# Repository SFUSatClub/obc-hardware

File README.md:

# OBC Hardware #

**demoboard_v1:** test board featuring RTC, flash memory, watchdog and SEL protection, to be tested with the TMS570LS0432 Launchpad board.

**OBC_prototypeA:** design for PC104 compliant OBC prototype, including onboard MCU, flash memory, SEL protection and power supplies. Includes all features of demoboard, interfaced to TMS570LS0714 MCU.

**Kicad-Lib:** SFUSat's common footprint and schematic symbol library.

## Getting started: ##
Clone this repo In the obc-hardware directory, run git submodule init In the obc-hardware directory, run git submodule update

Open KiCAD, navigate to the project you're interested in.
In EESchema, go to Preferences > Component Libraries
1. "Add" a user defined search path, select the KiCad-Lib directory in the obc-hardware directory
2. "Add" component library files and select the SFUSat.lib file in the KiCad-Lib folder
3. Press ok.

**Note:** issues may arise when using relative paths. Select absolute paths by choosing "No" when asked if you want to use a relative path

Exit back to the KiCad home window and go to Pcbnew > Preferences > Footprint Libraries Manager > "Project Specific Libraies" tab:

1. "Add Library"
2. Nickname: SFUSat
3. Library Path: ${KIPRJMOD}/KiCad-Lib/SFUSat.pretty

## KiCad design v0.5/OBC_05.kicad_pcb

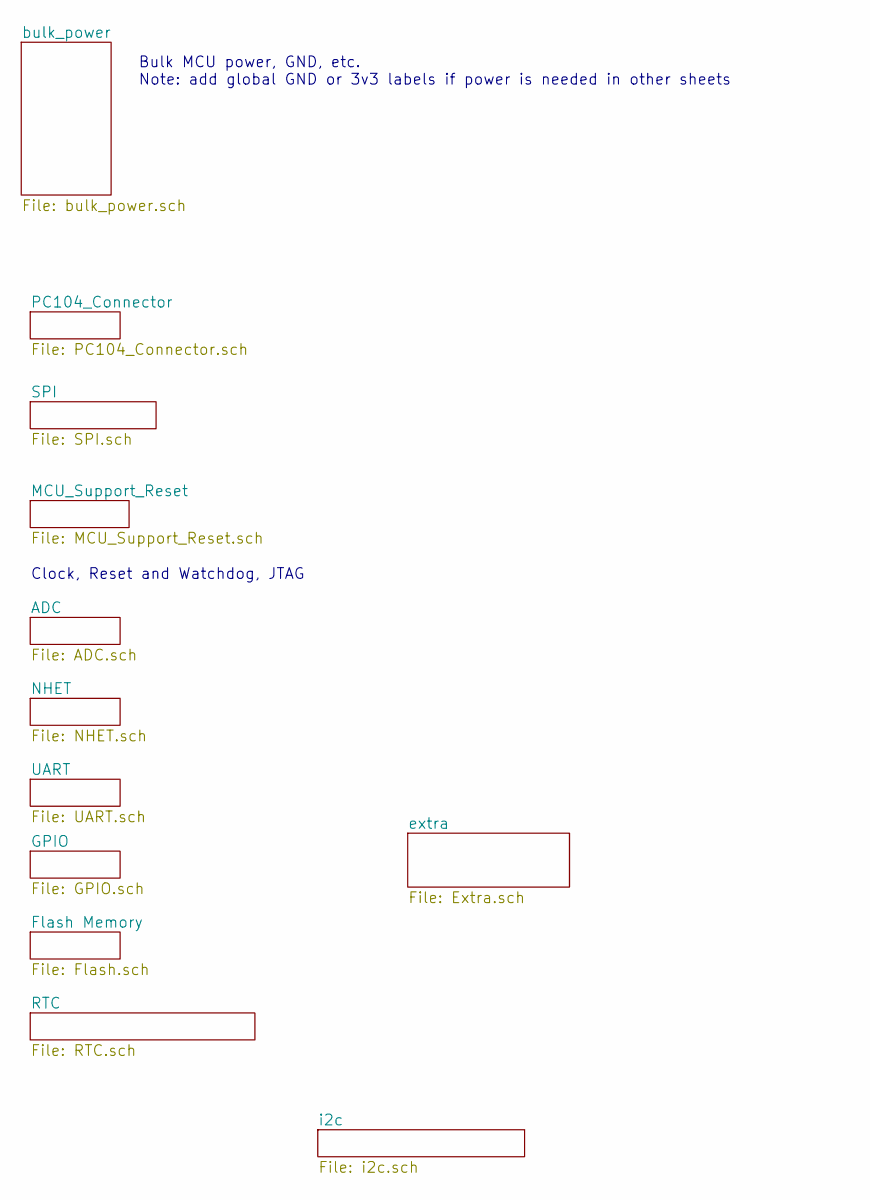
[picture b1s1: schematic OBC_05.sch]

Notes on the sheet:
Clock, Reset and Watchdog, JTAG
Bulk MCU power, GND, etc. Note: add global GND or 3v3 labels if power is needed in other sheets

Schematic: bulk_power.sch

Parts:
C2, C23: 1µF; C_0402
C3, C4, C5, C6, C7, C9, C10, C11, C12, C13, C14, C15, C16, C17, C18, C19, C20, C34, C35, C36: 0.1µF; C_0402
C21, C22: 4.7µF; C_0402
D1: LED; LED_0603
J2: Conn_01x02; 2x01In_Header_v2
P1: 3v3_IN_CONNECTOR; 2x01In_Header_v2
P2: INA_INPUT; 3x_01In_Header_v2
P3: INA_GND; 3x_01In_Header_v2
P4: INA_EN; 2x01In_Header_v2
P5: INA_OUTPUT; 2x01In_Header_v2
P12: LOAD; 2x01In_Header_v2
Q1, Q2: DMN2075U; SOT23_DMN2075U
Q3: 1v2_GOOD; SOT23_DMN2075U
R1: 7.5k; R_0402
R3: 0.04; R_2512
R4: 10k; R_0402
R5: 10K; R_0402
R6: 270; R_0402
U1: TMS570LS0714; LQFP-144_20x20mm_Pitch0.5mm
U2: MCP1825S; SOT-223
U3: AP7361_3.3v; SOT-223
U4: INA301; VSSOP_8

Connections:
1v2: C2.1, C4.1, C5.1, C6.1, C7.1, C9.1, C10.1, C11.1, C12.1, C13.1, C34.1, C35.1, C36.1, Q3.2 (G), R5.1, U1.17, U1.29, U1.45, U1.48, U1.49, U1.57, U1.87, U1.101, U1.114, U1.123, U1.137, U1.143, U2.3; also elsewhere on the board
3v3: C3.1, C14.2, C15.1, C16.1, C17.2, C18.1, C19.1, C20.1, C21.1, P2.3, P12.2, R3.2, R6.1, U1.10, U1.26, U1.42, U1.66, U1.69, U1.104, U1.120, U1.134, U1.136, U2.1, U4.7 (IN-); also elsewhere on the board
5v0: C23.1, U3.1; also elsewhere on the board
104_3v3: C22.1, J2.1, P1.1, P2.2, Q2.2 (G), U3.3; also elsewhere on the board
104_GND: P3.3, Q1.3 (S), Q2.3 (S), R1.2, U4.4 (GND), U4.5 (RESET); also elsewhere on the board
104_In_GND: C22.2, C23.2, J2.2, P1.2, Q2.1 (D), U3.2, U3.4; also elsewhere on the board
/MCU_Support_Reset/OSC_N: U1.20; also elsewhere on the board
/MCU_Support_Reset/OSC_P: U1.18; also elsewhere on the board
AD1_11: U1.75
AD1_12: U1.77
AD1_13: U1.79
AD1_14: U1.82
AD1_15: U1.85
AD1_16: U1.58
AD1_17: U1.59; also elsewhere on the board
AD1_18: U1.62; also elsewhere on the board
AD1_19: U1.63; also elsewhere on the board
AD1_20: U1.64; also elsewhere on the board
AD1_21: U1.65
AD1_22: U1.81
AD1_23: U1.84
FLASH0_CS: U1.105; also elsewhere on the board
FLASH1_CS: U1.130; also elsewhere on the board
FLASH2_CS: U1.40; also elsewhere on the board
FLASH_CLK: U1.95; also elsewhere on the board
FLASH_MISO: U1.94; also elsewhere on the board
FLASH_MOSI: U1.93; also elsewhere on the board
GIOA0: U1.2; also elsewhere on the board
GIOA1: U1.5; also elsewhere on the board
GIOA2: U1.9; also elsewhere on the board
GIOA6: U1.16; also elsewhere on the board
GIOB1: U1.133; also elsewhere on the board
GIOB2: U1.142; also elsewhere on the board
GIOB3: U1.1; also elsewhere on the board
GND: C2.2, C3.2, C4.2, C5.2, C6.2, C7.2, C9.2, C10.2, C11.2, C12.2, C13.2, C14.1, C15.2, C16.2, C17.1, C18.2, C19.2, C20.2, C21.2, C34.2, C35.2, C36.2, P3.2, P12.1, Q3.3 (S), R5.2, U1.11, U1.21, U1.27, U1.28, U1.34, U1.43, U1.44, U1.47, U1.50, U1.56, U1.67, U1.68, U1.88, U1.102, U1.103, U1.115, U1.121, U1.122, U1.135, U1.138, U1.144, U2.2, U2.4; also elsewhere on the board
I2C_SCL: U1.3; also elsewhere on the board
I2C_SDA: U1.4; also elsewhere on the board
INA_ALERT: P5.2, Q1.2 (G), R4.2, U4.6 (ALERT)
INA_INPUT: P2.1, P4.1, U4.1 (VS)
INA_OUT: P5.1, U1.73, U4.2 (OUT); also elsewhere on the board
LIN_RX: U1.131; also elsewhere on the board
LIN_TX: U1.132; also elsewhere on the board
MASTER_RESET: U1.46; also elsewhere on the board
unnamed 43: U1.19; also elsewhere on the board
unnamed 46: U1.116; also elsewhere on the board
unnamed: D1.1, Q3.1 (D)
unnamed: D1.2, R6.2
unnamed: P3.1, Q1.1 (D)
unnamed: P4.2, R3.1, R4.1, U4.8 (IN+)
unnamed: R1.1, U4.3 (LIMIT)
unnamed 104: U1.55; also elsewhere on the board
unnamed 115: U1.86; also elsewhere on the board
RF_CLK: U1.53; also elsewhere on the board
RF_CS: U1.37; also elsewhere on the board
RF_CS2: U1.6; also elsewhere on the board
RF_IRQ: U1.14; also elsewhere on the board
RF_MISO: U1.51; also elsewhere on the board
RF_MOSI: U1.52; also elsewhere on the board
RTCK: U1.113
RTC_CLK: U1.100; also elsewhere on the board
RTC_CS: U1.32; also elsewhere on the board
RTC_MISO: U1.98; also elsewhere on the board
RTC_MOSI: U1.99; also elsewhere on the board
TCK: U1.112; also elsewhere on the board
TDI: U1.110; also elsewhere on the board
TDO: U1.111; also elsewhere on the board
TMS: U1.108; also elsewhere on the board
UART_RX: U1.38; also elsewhere on the board
UART_TX: U1.39; also elsewhere on the board
WATCHDOG: U1.126; also elsewhere on the board
nERROR: U1.117; also elsewhere on the board
nTRST: U1.109; also elsewhere on the board
xGPIO0: U1.23; also elsewhere on the board
xGPIO1: U1.30; also elsewhere on the board
xGPIO2: U1.31; also elsewhere on the board
xGPIO3: U1.97; also elsewhere on the board
xGPIO4: U1.96; also elsewhere on the board
xGPIO5: U1.91; also elsewhere on the board
xGPIO6: U1.41; also elsewhere on the board
xGPIO7: U1.22; also elsewhere on the board
xGPIO8: U1.106; also elsewhere on the board
xGPIO9: U1.90; also elsewhere on the board
xGPIO10: U1.89; also elsewhere on the board
xGPIO11: U1.129; also elsewhere on the board
xGPIO12: U1.128; also elsewhere on the board
xNHET0: U1.15; also elsewhere on the board
xNHET1: U1.92; also elsewhere on the board

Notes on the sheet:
1.2v regulator
Use this connector to enable or disable INA control
2+3 closed: INA Disabled 2+1 closed: INA Enabled
reverse polarity fet
SEL Protection FET
C8 were removed at the board level, as multiple pins were connected to one cap.
For load testing the current limit
INA_POWER_ENABLE Short this connector if using INA Prevents INA from being powered when it is supposed to be disconnected
OBC power header for flexibility if 104 is blocked
Either use 3V3 from 104 (or our power header, they're identical), or short USB_5V and don't have any 3V3 on the 104 connector or our power header.
Either connect 3v3 before shunt to the top end of the shunt, or we bypass the shunt and connect right to 3V3 net.
Extra 3V3 input located in satellite access hole

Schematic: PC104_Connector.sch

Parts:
C8: 100nF; C_0402
C33: 10nF; C_0402
C37, C38: 47pF; C_0402
D4: TX; LED_0603
D5: RX; LED_0603
J1: PC104-8BIT; PC104-8bit
P6: USB_PORT; USB_MINIB_SMD
P11: USB_5V; 2x01In_Header_v2
R2, R31: 27; R_0402
R32, R33, R34, R35: 10k; R_0402
R36, R37: 270; R_0402
R38, R39, R40, R41: 0; R_0402
U10: FTDI_SSOP; 16-SSOP
W1: TEST_1P; Test_Point

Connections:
3v3: C8.1, R32.1, R33.1, R34.1, R35.1, R36.1, R37.1, U10.3, U10.10, U10.11, U10.12; also elsewhere on the board
5v0: P11.1; also elsewhere on the board
104_3v3: J1.3B, J1.29B; also elsewhere on the board
104_In_GND: C8.2, C33.2, C37.2, C38.2, J1.1B, J1.31B, J1.32A, J1.32B, P6.5, U10.5, U10.13, W1.1; also elsewhere on the board
AD1_17: J1.23B; also elsewhere on the board
AD1_18: J1.24B; also elsewhere on the board
AD1_19: J1.25B; also elsewhere on the board
AD1_20: J1.26B; also elsewhere on the board
GIOA0: J1.7B; also elsewhere on the board
GIOA1: J1.8B; also elsewhere on the board
GIOA2: J1.9B; also elsewhere on the board
GIOB1: J1.10B; also elsewhere on the board
GIOB2: J1.11B; also elsewhere on the board
GIOB3: J1.12B; also elsewhere on the board
I2C_SCL: J1.18B; also elsewhere on the board
I2C_SDA: J1.17B; also elsewhere on the board
LIN_RX: R39.2, R40.2; also elsewhere on the board
LIN_TX: R38.2, R41.2; also elsewhere on the board
unnamed: D4.1, U10.14
unnamed: D4.2, R36.2
unnamed: D5.1, U10.7
unnamed: D5.2, R37.2
unnamed: J1.19B, R40.1, R41.1
unnamed: J1.20B, R38.1, R39.1
unnamed: R2.1, U10.9
unnamed: R31.1, U10.8
unnamed: R34.2, U10.2
unnamed: R35.2, U10.6
RF_CLK: J1.1A; also elsewhere on the board
RF_CS: J1.4A; also elsewhere on the board
RF_CS2: J1.6A; also elsewhere on the board
RF_IRQ: J1.5A; also elsewhere on the board
RF_MISO: J1.3A; also elsewhere on the board
RF_MOSI: J1.2A; also elsewhere on the board
UART_RX: J1.5B, R32.2, U10.1; also elsewhere on the board
UART_TX: J1.6B, R33.2, U10.4; also elsewhere on the board
USB_5V: C33.1, P6.1, P11.2
USB_N: C37.1, P6.2, R2.2
USB_P: C38.1, P6.3, R31.2
xGPIO0: J1.12A; also elsewhere on the board
xGPIO1: J1.13A; also elsewhere on the board
xGPIO2: J1.19A; also elsewhere on the board
xGPIO3: J1.20A; also elsewhere on the board
xGPIO4: J1.21A; also elsewhere on the board
xGPIO5: J1.22A; also elsewhere on the board
xGPIO6: J1.15B; also elsewhere on the board
xGPIO7: J1.14B; also elsewhere on the board
xGPIO8: J1.13B; also elsewhere on the board
xGPIO9: J1.7A; also elsewhere on the board
xGPIO10: J1.8A; also elsewhere on the board
xGPIO11: J1.9A; also elsewhere on the board
xGPIO12: J1.10A; also elsewhere on the board
xNHET0: J1.14A; also elsewhere on the board
xNHET1: J1.15A; also elsewhere on the board

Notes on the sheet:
Global Power Needed to connect power on the different sheets
Grounding: 104_GND is connected either to "GND" net directly, or to GND net through the FET, allowing the load to be switched by the SEL mitigation circuit. This is selected by a jumper on the power page.
RF_Deploy0
GPS_RST
GIOA5 - Support Reset, CLK Section
Sun Sensors
RF_Deploy1
EPS_CHRG_OK
EPS_PROCHP
RF_IRQ2
USB 5V jumper: - if shorted, we use 5V from USB and regulate to 3.3 onboard - otherwise: we use 3.3 from the 104 connector
Connect 0Ω on 41 and 39 or 38 and 40. Default (expected) config is 0Ω on even labels

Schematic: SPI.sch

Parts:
U1: TMS570LS0714; LQFP-144_20x20mm_Pitch0.5mm

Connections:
1v2: U1.17, U1.29, U1.45, U1.48, U1.49, U1.57, U1.87, U1.101, U1.114, U1.123, U1.137, U1.143; also elsewhere on the board
3v3: U1.10, U1.26, U1.42, U1.66, U1.69, U1.104, U1.120, U1.134, U1.136; also elsewhere on the board
/MCU_Support_Reset/OSC_N: U1.20; also elsewhere on the board
/MCU_Support_Reset/OSC_P: U1.18; also elsewhere on the board
AD1_11: U1.75
AD1_12: U1.77
AD1_13: U1.79
AD1_14: U1.82
AD1_15: U1.85
AD1_16: U1.58
AD1_17: U1.59; also elsewhere on the board
AD1_18: U1.62; also elsewhere on the board
AD1_19: U1.63; also elsewhere on the board
AD1_20: U1.64; also elsewhere on the board
AD1_21: U1.65
AD1_22: U1.81
AD1_23: U1.84
FLASH0_CS: U1.105; also elsewhere on the board
FLASH1_CS: U1.130; also elsewhere on the board
FLASH2_CS: U1.40; also elsewhere on the board
FLASH_CLK: U1.95; also elsewhere on the board
FLASH_MISO: U1.94; also elsewhere on the board
FLASH_MOSI: U1.93; also elsewhere on the board
GIOA0: U1.2; also elsewhere on the board
GIOA1: U1.5; also elsewhere on the board
GIOA2: U1.9; also elsewhere on the board
GIOA6: U1.16; also elsewhere on the board
GIOB1: U1.133; also elsewhere on the board
GIOB2: U1.142; also elsewhere on the board
GIOB3: U1.1; also elsewhere on the board
GND: U1.11, U1.21, U1.27, U1.28, U1.34, U1.43, U1.44, U1.47, U1.50, U1.56, U1.67, U1.68, U1.88, U1.102, U1.103, U1.115, U1.121, U1.122, U1.135, U1.138, U1.144; also elsewhere on the board
I2C_SCL: U1.3; also elsewhere on the board
I2C_SDA: U1.4; also elsewhere on the board
INA_OUT: U1.73; also elsewhere on the board
LIN_RX: U1.131; also elsewhere on the board
LIN_TX: U1.132; also elsewhere on the board
MASTER_RESET: U1.46; also elsewhere on the board
unnamed 43: U1.19; also elsewhere on the board
unnamed 46: U1.116; also elsewhere on the board
unnamed 104: U1.55; also elsewhere on the board
unnamed 115: U1.86; also elsewhere on the board
RF_CLK: U1.53; also elsewhere on the board
RF_CS: U1.37; also elsewhere on the board
RF_CS2: U1.6; also elsewhere on the board
RF_IRQ: U1.14; also elsewhere on the board
RF_MISO: U1.51; also elsewhere on the board
RF_MOSI: U1.52; also elsewhere on the board
RTCK: U1.113
RTC_CLK: U1.100; also elsewhere on the board
RTC_CS: U1.32; also elsewhere on the board
RTC_MISO: U1.98; also elsewhere on the board
RTC_MOSI: U1.99; also elsewhere on the board
TCK: U1.112; also elsewhere on the board
TDI: U1.110; also elsewhere on the board
TDO: U1.111; also elsewhere on the board
TMS: U1.108; also elsewhere on the board
UART_RX: U1.38; also elsewhere on the board
UART_TX: U1.39; also elsewhere on the board
WATCHDOG: U1.126; also elsewhere on the board
nERROR: U1.117; also elsewhere on the board
nTRST: U1.109; also elsewhere on the board
xGPIO0: U1.23; also elsewhere on the board
xGPIO1: U1.30; also elsewhere on the board
xGPIO2: U1.31; also elsewhere on the board
xGPIO3: U1.97; also elsewhere on the board
xGPIO4: U1.96; also elsewhere on the board
xGPIO5: U1.91; also elsewhere on the board
xGPIO6: U1.41; also elsewhere on the board
xGPIO7: U1.22; also elsewhere on the board
xGPIO8: U1.106; also elsewhere on the board
xGPIO9: U1.90; also elsewhere on the board
xGPIO10: U1.89; also elsewhere on the board
xGPIO11: U1.129; also elsewhere on the board
xGPIO12: U1.128; also elsewhere on the board
xNHET0: U1.15; also elsewhere on the board
xNHET1: U1.92; also elsewhere on the board

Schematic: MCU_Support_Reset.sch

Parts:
C1, C31, C32: 0.1µF; C_0402
C27, C28: 33pF; C_0402
P13: WD_EN; 2x01In_Header_v2
P14: WD_RST_DIS; 2x01In_Header_v2
P16: JTAG_10PIN; JTAG_10pin_1.27mm
Q4: DMN2075U; SOT23_DMN2075U
R8, R25: 10k; R_0402
R22: 200k; R_0402
R23: 187k; R_0402
R24: 2.2k; R_0402
SW1, SW2, SW4: SPST; Tact_SW_SMD_v2
U1: TMS570LS0714; LQFP-144_20x20mm_Pitch0.5mm
U9: TPS3110; SOT_23_6
U11: STLM75; TSSOP-8-3x3mm-SOT505-1
W2: MASTER_RST; Test_Point
W12: nERROR; Test_Point
W14: RESET_TEST; Test_Point
Y1: XTAL; SMD_XTAL

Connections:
1v2: R22.1, U1.17, U1.29, U1.45, U1.48, U1.49, U1.57, U1.87, U1.101, U1.114, U1.123, U1.137, U1.143; also elsewhere on the board
3v3: C1.1, P13.2, P16.1, R8.1, R24.1, R25.1, U1.10, U1.26, U1.42, U1.66, U1.69, U1.104, U1.120, U1.134, U1.136, U11.8; also elsewhere on the board
/MCU_Support_Reset/OSC_N: C28.2, U1.20, Y1.2
/MCU_Support_Reset/OSC_P: C27.1, U1.18, Y1.1
AD1_11: U1.75
AD1_12: U1.77
AD1_13: U1.79
AD1_14: U1.82
AD1_15: U1.85
AD1_16: U1.58
AD1_17: U1.59; also elsewhere on the board
AD1_18: U1.62; also elsewhere on the board
AD1_19: U1.63; also elsewhere on the board
AD1_20: U1.64; also elsewhere on the board
AD1_21: U1.65
AD1_22: U1.81
AD1_23: U1.84
FLASH0_CS: U1.105; also elsewhere on the board
FLASH1_CS: U1.130; also elsewhere on the board
FLASH2_CS: U1.40; also elsewhere on the board
FLASH_CLK: U1.95; also elsewhere on the board
FLASH_MISO: U1.94; also elsewhere on the board
FLASH_MOSI: U1.93; also elsewhere on the board
GIOA0: U1.2; also elsewhere on the board
GIOA1: U1.5; also elsewhere on the board
GIOA2: U1.9; also elsewhere on the board
GIOA6: U1.16; also elsewhere on the board
GIOB1: U1.133; also elsewhere on the board
GIOB2: U1.142; also elsewhere on the board
GIOB3: U1.1; also elsewhere on the board
GND: C1.2, C31.2, C32.2, P14.1, P16.3, P16.5, R23.2, SW1.2, SW2.2, SW4.2, U1.11, U1.21, U1.27, U1.28, U1.34, U1.43, U1.44, U1.47, U1.50, U1.56, U1.67, U1.68, U1.88, U1.102, U1.103, U1.115, U1.121, U1.122, U1.135, U1.138, U1.144, U9.2 (GND), U11.4, U11.5, U11.6, U11.7; also elsewhere on the board
I2C_SCL: U1.3, U11.2; also elsewhere on the board
I2C_SDA: U1.4, U11.1; also elsewhere on the board
INA_OUT: U1.73; also elsewhere on the board
LIN_RX: U1.131; also elsewhere on the board
LIN_TX: U1.132; also elsewhere on the board
MASTER_RESET: P16.10, Q4.1 (D), R24.2, SW4.1, U1.46, W2.1
unnamed: C27.2, C28.1, U1.19
unnamed: C31.1, P13.1, U9.6 (VDD)
unnamed: C32.1, R25.2, SW2.1, U1.116
unnamed: P14.2, Q4.2 (G), R8.2
unnamed: Q4.3 (S), U9.1 (RESET), W14.1
unnamed: R22.2, R23.1, U9.4 (SENSE)
unnamed: SW1.1, U9.3 (MR)
unnamed 104: U1.55; also elsewhere on the board
unnamed 115: U1.86; also elsewhere on the board
RF_CLK: U1.53; also elsewhere on the board
RF_CS: U1.37; also elsewhere on the board
RF_CS2: U1.6; also elsewhere on the board
RF_IRQ: U1.14; also elsewhere on the board
RF_MISO: U1.51; also elsewhere on the board
RF_MOSI: U1.52; also elsewhere on the board
RTCK: U1.113
RTC_CLK: U1.100; also elsewhere on the board
RTC_CS: U1.32; also elsewhere on the board
RTC_MISO: U1.98; also elsewhere on the board
RTC_MOSI: U1.99; also elsewhere on the board
TCK: P16.4, U1.112
TDI: P16.8, U1.110
TDO: P16.6, U1.111
TMS: P16.2, U1.108
UART_RX: U1.38; also elsewhere on the board
UART_TX: U1.39; also elsewhere on the board
WATCHDOG: U1.126, U9.5 (WDI); also elsewhere on the board
nERROR: U1.117, W12.1
nTRST: P16.7, U1.109
xGPIO0: U1.23; also elsewhere on the board
xGPIO1: U1.30; also elsewhere on the board
xGPIO2: U1.31; also elsewhere on the board
xGPIO3: U1.97; also elsewhere on the board
xGPIO4: U1.96; also elsewhere on the board
xGPIO5: U1.91; also elsewhere on the board
xGPIO6: U1.41; also elsewhere on the board
xGPIO7: U1.22; also elsewhere on the board
xGPIO8: U1.106; also elsewhere on the board
xGPIO9: U1.90; also elsewhere on the board
xGPIO10: U1.89; also elsewhere on the board
xGPIO11: U1.129; also elsewhere on the board
xGPIO12: U1.128; also elsewhere on the board
xNHET0: U1.15; also elsewhere on the board
xNHET1: U1.92; also elsewhere on the board

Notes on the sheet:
nPORRST is hard reset
Soft Reset
Hard reset via WD
Temperature Sensor Address = 0
Hard reset
R25 is not populated in 0.3
Program mode: short jumper, watchdog is disabled Space mode: open jumper, watchdog is enabled

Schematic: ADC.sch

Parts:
R7: 10k; R_0402
U1: TMS570LS0714; LQFP-144_20x20mm_Pitch0.5mm
W7: AD1EVT1; Test_Point
W8: GIOB2; Test_Point

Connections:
1v2: U1.17, U1.29, U1.45, U1.48, U1.49, U1.57, U1.87, U1.101, U1.114, U1.123, U1.137, U1.143; also elsewhere on the board
3v3: U1.10, U1.26, U1.42, U1.66, U1.69, U1.104, U1.120, U1.134, U1.136; also elsewhere on the board
104_GND: R7.2; also elsewhere on the board
/MCU_Support_Reset/OSC_N: U1.20; also elsewhere on the board
/MCU_Support_Reset/OSC_P: U1.18; also elsewhere on the board
AD1_11: U1.75
AD1_12: U1.77
AD1_13: U1.79
AD1_14: U1.82
AD1_15: U1.85
AD1_16: U1.58
AD1_17: U1.59; also elsewhere on the board
AD1_18: U1.62; also elsewhere on the board
AD1_19: U1.63; also elsewhere on the board
AD1_20: U1.64; also elsewhere on the board
AD1_21: U1.65
AD1_22: U1.81
AD1_23: U1.84
FLASH0_CS: U1.105; also elsewhere on the board
FLASH1_CS: U1.130; also elsewhere on the board
FLASH2_CS: U1.40; also elsewhere on the board
FLASH_CLK: U1.95; also elsewhere on the board
FLASH_MISO: U1.94; also elsewhere on the board
FLASH_MOSI: U1.93; also elsewhere on the board
GIOA0: U1.2; also elsewhere on the board
GIOA1: U1.5; also elsewhere on the board
GIOA2: U1.9; also elsewhere on the board
GIOA6: U1.16; also elsewhere on the board
GIOB1: U1.133; also elsewhere on the board
GIOB2: U1.142; also elsewhere on the board
GIOB3: U1.1; also elsewhere on the board
GND: U1.11, U1.21, U1.27, U1.28, U1.34, U1.43, U1.44, U1.47, U1.50, U1.56, U1.67, U1.68, U1.88, U1.102, U1.103, U1.115, U1.121, U1.122, U1.135, U1.138, U1.144; also elsewhere on the board
I2C_SCL: U1.3; also elsewhere on the board
I2C_SDA: U1.4; also elsewhere on the board
INA_OUT: R7.1, U1.73; also elsewhere on the board
LIN_RX: U1.131; also elsewhere on the board
LIN_TX: U1.132; also elsewhere on the board
MASTER_RESET: U1.46; also elsewhere on the board
unnamed 43: U1.19; also elsewhere on the board
unnamed 46: U1.116; also elsewhere on the board
unnamed: U1.55, W8.1
unnamed: U1.86, W7.1
RF_CLK: U1.53; also elsewhere on the board
RF_CS: U1.37; also elsewhere on the board
RF_CS2: U1.6; also elsewhere on the board
RF_IRQ: U1.14; also elsewhere on the board
RF_MISO: U1.51; also elsewhere on the board
RF_MOSI: U1.52; also elsewhere on the board
RTCK: U1.113
RTC_CLK: U1.100; also elsewhere on the board
RTC_CS: U1.32; also elsewhere on the board
RTC_MISO: U1.98; also elsewhere on the board
RTC_MOSI: U1.99; also elsewhere on the board
TCK: U1.112; also elsewhere on the board
TDI: U1.110; also elsewhere on the board
TDO: U1.111; also elsewhere on the board
TMS: U1.108; also elsewhere on the board
UART_RX: U1.38; also elsewhere on the board
UART_TX: U1.39; also elsewhere on the board
WATCHDOG: U1.126; also elsewhere on the board
nERROR: U1.117; also elsewhere on the board
nTRST: U1.109; also elsewhere on the board
xGPIO0: U1.23; also elsewhere on the board
xGPIO1: U1.30; also elsewhere on the board
xGPIO2: U1.31; also elsewhere on the board
xGPIO3: U1.97; also elsewhere on the board
xGPIO4: U1.96; also elsewhere on the board
xGPIO5: U1.91; also elsewhere on the board
xGPIO6: U1.41; also elsewhere on the board
xGPIO7: U1.22; also elsewhere on the board
xGPIO8: U1.106; also elsewhere on the board
xGPIO9: U1.90; also elsewhere on the board
xGPIO10: U1.89; also elsewhere on the board
xGPIO11: U1.129; also elsewhere on the board
xGPIO12: U1.128; also elsewhere on the board
xNHET0: U1.15; also elsewhere on the board
xNHET1: U1.92; also elsewhere on the board

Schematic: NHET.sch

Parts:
U1: TMS570LS0714; LQFP-144_20x20mm_Pitch0.5mm

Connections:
1v2: U1.17, U1.29, U1.45, U1.48, U1.49, U1.57, U1.87, U1.101, U1.114, U1.123, U1.137, U1.143; also elsewhere on the board
3v3: U1.10, U1.26, U1.42, U1.66, U1.69, U1.104, U1.120, U1.134, U1.136; also elsewhere on the board
/MCU_Support_Reset/OSC_N: U1.20; also elsewhere on the board
/MCU_Support_Reset/OSC_P: U1.18; also elsewhere on the board
AD1_11: U1.75
AD1_12: U1.77
AD1_13: U1.79
AD1_14: U1.82
AD1_15: U1.85
AD1_16: U1.58
AD1_17: U1.59; also elsewhere on the board
AD1_18: U1.62; also elsewhere on the board
AD1_19: U1.63; also elsewhere on the board
AD1_20: U1.64; also elsewhere on the board
AD1_21: U1.65
AD1_22: U1.81
AD1_23: U1.84
FLASH0_CS: U1.105; also elsewhere on the board
FLASH1_CS: U1.130; also elsewhere on the board
FLASH2_CS: U1.40; also elsewhere on the board
FLASH_CLK: U1.95; also elsewhere on the board
FLASH_MISO: U1.94; also elsewhere on the board
FLASH_MOSI: U1.93; also elsewhere on the board
GIOA0: U1.2; also elsewhere on the board
GIOA1: U1.5; also elsewhere on the board
GIOA2: U1.9; also elsewhere on the board
GIOA6: U1.16; also elsewhere on the board
GIOB1: U1.133; also elsewhere on the board
GIOB2: U1.142; also elsewhere on the board
GIOB3: U1.1; also elsewhere on the board
GND: U1.11, U1.21, U1.27, U1.28, U1.34, U1.43, U1.44, U1.47, U1.50, U1.56, U1.67, U1.68, U1.88, U1.102, U1.103, U1.115, U1.121, U1.122, U1.135, U1.138, U1.144; also elsewhere on the board
I2C_SCL: U1.3; also elsewhere on the board
I2C_SDA: U1.4; also elsewhere on the board
INA_OUT: U1.73; also elsewhere on the board
LIN_RX: U1.131; also elsewhere on the board
LIN_TX: U1.132; also elsewhere on the board
MASTER_RESET: U1.46; also elsewhere on the board
unnamed 43: U1.19; also elsewhere on the board
unnamed 46: U1.116; also elsewhere on the board
unnamed 104: U1.55; also elsewhere on the board
unnamed 115: U1.86; also elsewhere on the board
RF_CLK: U1.53; also elsewhere on the board
RF_CS: U1.37; also elsewhere on the board
RF_CS2: U1.6; also elsewhere on the board
RF_IRQ: U1.14; also elsewhere on the board
RF_MISO: U1.51; also elsewhere on the board
RF_MOSI: U1.52; also elsewhere on the board
RTCK: U1.113
RTC_CLK: U1.100; also elsewhere on the board
RTC_CS: U1.32; also elsewhere on the board
RTC_MISO: U1.98; also elsewhere on the board
RTC_MOSI: U1.99; also elsewhere on the board
TCK: U1.112; also elsewhere on the board
TDI: U1.110; also elsewhere on the board
TDO: U1.111; also elsewhere on the board
TMS: U1.108; also elsewhere on the board
UART_RX: U1.38; also elsewhere on the board
UART_TX: U1.39; also elsewhere on the board
WATCHDOG: U1.126; also elsewhere on the board
nERROR: U1.117; also elsewhere on the board
nTRST: U1.109; also elsewhere on the board
xGPIO0: U1.23; also elsewhere on the board
xGPIO1: U1.30; also elsewhere on the board
xGPIO2: U1.31; also elsewhere on the board
xGPIO3: U1.97; also elsewhere on the board
xGPIO4: U1.96; also elsewhere on the board
xGPIO5: U1.91; also elsewhere on the board
xGPIO6: U1.41; also elsewhere on the board
xGPIO7: U1.22; also elsewhere on the board
xGPIO8: U1.106; also elsewhere on the board
xGPIO9: U1.90; also elsewhere on the board
xGPIO10: U1.89; also elsewhere on the board
xGPIO11: U1.129; also elsewhere on the board
xGPIO12: U1.128; also elsewhere on the board
xNHET0: U1.15; also elsewhere on the board
xNHET1: U1.92; also elsewhere on the board

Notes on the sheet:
Spare NHET in case we need to turn them into a UART or i2c or something

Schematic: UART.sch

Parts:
U1: TMS570LS0714; LQFP-144_20x20mm_Pitch0.5mm

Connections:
1v2: U1.17, U1.29, U1.45, U1.48, U1.49, U1.57, U1.87, U1.101, U1.114, U1.123, U1.137, U1.143; also elsewhere on the board
3v3: U1.10, U1.26, U1.42, U1.66, U1.69, U1.104, U1.120, U1.134, U1.136; also elsewhere on the board
/MCU_Support_Reset/OSC_N: U1.20; also elsewhere on the board
/MCU_Support_Reset/OSC_P: U1.18; also elsewhere on the board
AD1_11: U1.75
AD1_12: U1.77
AD1_13: U1.79
AD1_14: U1.82
AD1_15: U1.85
AD1_16: U1.58
AD1_17: U1.59; also elsewhere on the board
AD1_18: U1.62; also elsewhere on the board
AD1_19: U1.63; also elsewhere on the board
AD1_20: U1.64; also elsewhere on the board
AD1_21: U1.65
AD1_22: U1.81
AD1_23: U1.84
FLASH0_CS: U1.105; also elsewhere on the board
FLASH1_CS: U1.130; also elsewhere on the board
FLASH2_CS: U1.40; also elsewhere on the board
FLASH_CLK: U1.95; also elsewhere on the board
FLASH_MISO: U1.94; also elsewhere on the board
FLASH_MOSI: U1.93; also elsewhere on the board
GIOA0: U1.2; also elsewhere on the board
GIOA1: U1.5; also elsewhere on the board
GIOA2: U1.9; also elsewhere on the board
GIOA6: U1.16; also elsewhere on the board
GIOB1: U1.133; also elsewhere on the board
GIOB2: U1.142; also elsewhere on the board
GIOB3: U1.1; also elsewhere on the board
GND: U1.11, U1.21, U1.27, U1.28, U1.34, U1.43, U1.44, U1.47, U1.50, U1.56, U1.67, U1.68, U1.88, U1.102, U1.103, U1.115, U1.121, U1.122, U1.135, U1.138, U1.144; also elsewhere on the board
I2C_SCL: U1.3; also elsewhere on the board
I2C_SDA: U1.4; also elsewhere on the board
INA_OUT: U1.73; also elsewhere on the board
LIN_RX: U1.131; also elsewhere on the board
LIN_TX: U1.132; also elsewhere on the board
MASTER_RESET: U1.46; also elsewhere on the board
unnamed 43: U1.19; also elsewhere on the board
unnamed 46: U1.116; also elsewhere on the board
unnamed 104: U1.55; also elsewhere on the board
unnamed 115: U1.86; also elsewhere on the board
RF_CLK: U1.53; also elsewhere on the board
RF_CS: U1.37; also elsewhere on the board
RF_CS2: U1.6; also elsewhere on the board
RF_IRQ: U1.14; also elsewhere on the board
RF_MISO: U1.51; also elsewhere on the board
RF_MOSI: U1.52; also elsewhere on the board
RTCK: U1.113
RTC_CLK: U1.100; also elsewhere on the board
RTC_CS: U1.32; also elsewhere on the board
RTC_MISO: U1.98; also elsewhere on the board
RTC_MOSI: U1.99; also elsewhere on the board
TCK: U1.112; also elsewhere on the board
TDI: U1.110; also elsewhere on the board
TDO: U1.111; also elsewhere on the board
TMS: U1.108; also elsewhere on the board
UART_RX: U1.38; also elsewhere on the board
UART_TX: U1.39; also elsewhere on the board
WATCHDOG: U1.126; also elsewhere on the board
nERROR: U1.117; also elsewhere on the board
nTRST: U1.109; also elsewhere on the board
xGPIO0: U1.23; also elsewhere on the board
xGPIO1: U1.30; also elsewhere on the board
xGPIO2: U1.31; also elsewhere on the board
xGPIO3: U1.97; also elsewhere on the board
xGPIO4: U1.96; also elsewhere on the board
xGPIO5: U1.91; also elsewhere on the board
xGPIO6: U1.41; also elsewhere on the board
xGPIO7: U1.22; also elsewhere on the board
xGPIO8: U1.106; also elsewhere on the board
xGPIO9: U1.90; also elsewhere on the board
xGPIO10: U1.89; also elsewhere on the board
xGPIO11: U1.129; also elsewhere on the board
xGPIO12: U1.128; also elsewhere on the board
xNHET0: U1.15; also elsewhere on the board
xNHET1: U1.92; also elsewhere on the board

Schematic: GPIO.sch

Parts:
D3: LED; LED_0603
Q5: DMN2075U; SOT23_DMN2075U
R9: 270; R_0402
R26: 10k; R_0402
U1: TMS570LS0714; LQFP-144_20x20mm_Pitch0.5mm
W13: WD_TEST; Test_Point

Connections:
1v2: U1.17, U1.29, U1.45, U1.48, U1.49, U1.57, U1.87, U1.101, U1.114, U1.123, U1.137, U1.143; also elsewhere on the board
3v3: R9.1, U1.10, U1.26, U1.42, U1.66, U1.69, U1.104, U1.120, U1.134, U1.136; also elsewhere on the board
/MCU_Support_Reset/OSC_N: U1.20; also elsewhere on the board
/MCU_Support_Reset/OSC_P: U1.18; also elsewhere on the board
AD1_11: U1.75
AD1_12: U1.77
AD1_13: U1.79
AD1_14: U1.82
AD1_15: U1.85
AD1_16: U1.58
AD1_17: U1.59; also elsewhere on the board
AD1_18: U1.62; also elsewhere on the board
AD1_19: U1.63; also elsewhere on the board
AD1_20: U1.64; also elsewhere on the board
AD1_21: U1.65
AD1_22: U1.81
AD1_23: U1.84
FLASH0_CS: U1.105; also elsewhere on the board
FLASH1_CS: U1.130; also elsewhere on the board
FLASH2_CS: U1.40; also elsewhere on the board
FLASH_CLK: U1.95; also elsewhere on the board
FLASH_MISO: U1.94; also elsewhere on the board
FLASH_MOSI: U1.93; also elsewhere on the board
GIOA0: U1.2; also elsewhere on the board
GIOA1: U1.5; also elsewhere on the board
GIOA2: U1.9; also elsewhere on the board
GIOA6: Q5.2 (G), U1.16
GIOB1: U1.133; also elsewhere on the board
GIOB2: U1.142; also elsewhere on the board
GIOB3: U1.1; also elsewhere on the board
GND: Q5.3 (S), R26.2, U1.11, U1.21, U1.27, U1.28, U1.34, U1.43, U1.44, U1.47, U1.50, U1.56, U1.67, U1.68, U1.88, U1.102, U1.103, U1.115, U1.121, U1.122, U1.135, U1.138, U1.144; also elsewhere on the board
I2C_SCL: U1.3; also elsewhere on the board
I2C_SDA: U1.4; also elsewhere on the board
INA_OUT: U1.73; also elsewhere on the board
LIN_RX: U1.131; also elsewhere on the board
LIN_TX: U1.132; also elsewhere on the board
MASTER_RESET: U1.46; also elsewhere on the board
unnamed 43: U1.19; also elsewhere on the board
unnamed 46: U1.116; also elsewhere on the board
unnamed: D3.1, Q5.1 (D)
unnamed: D3.2, R9.2
unnamed 104: U1.55; also elsewhere on the board
unnamed 115: U1.86; also elsewhere on the board
RF_CLK: U1.53; also elsewhere on the board
RF_CS: U1.37; also elsewhere on the board
RF_CS2: U1.6; also elsewhere on the board
RF_IRQ: U1.14; also elsewhere on the board
RF_MISO: U1.51; also elsewhere on the board
RF_MOSI: U1.52; also elsewhere on the board
RTCK: U1.113
RTC_CLK: U1.100; also elsewhere on the board
RTC_CS: U1.32; also elsewhere on the board
RTC_MISO: U1.98; also elsewhere on the board
RTC_MOSI: U1.99; also elsewhere on the board
TCK: U1.112; also elsewhere on the board
TDI: U1.110; also elsewhere on the board
TDO: U1.111; also elsewhere on the board
TMS: U1.108; also elsewhere on the board
UART_RX: U1.38; also elsewhere on the board
UART_TX: U1.39; also elsewhere on the board
WATCHDOG: R26.1, U1.126, W13.1; also elsewhere on the board
nERROR: U1.117; also elsewhere on the board
nTRST: U1.109; also elsewhere on the board
xGPIO0: U1.23; also elsewhere on the board
xGPIO1: U1.30; also elsewhere on the board
xGPIO2: U1.31; also elsewhere on the board
xGPIO3: U1.97; also elsewhere on the board
xGPIO4: U1.96; also elsewhere on the board
xGPIO5: U1.91; also elsewhere on the board
xGPIO6: U1.41; also elsewhere on the board
xGPIO7: U1.22; also elsewhere on the board
xGPIO8: U1.106; also elsewhere on the board
xGPIO9: U1.90; also elsewhere on the board
xGPIO10: U1.89; also elsewhere on the board
xGPIO11: U1.129; also elsewhere on the board
xGPIO12: U1.128; also elsewhere on the board
xNHET0: U1.15; also elsewhere on the board
xNHET1: U1.92; also elsewhere on the board

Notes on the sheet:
"Pin 16 LED" - for blinky debug
RTC_INT
RF.DEPLOY
BLINKY

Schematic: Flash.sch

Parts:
C24, C25, C26: 0.1µF; C_0402
P9: FLASH_SPI; 3x_01In_Header_v2
P10: FLASH_CS; 3x_01In_Header_v2
R13, R17, R21: 10k; R_0402
U5, U6, U7: FLASH_IS25LP016D; SOT-8_208mil_medium

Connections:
3v3: C24.2, C25.2, C26.2, R13.1, R17.1, R21.1, U5.3, U5.8, U6.3, U6.8, U7.3, U7.8; also elsewhere on the board
FLASH0_CS: P10.3, U5.1; also elsewhere on the board
FLASH1_CS: P10.2, U6.1; also elsewhere on the board
FLASH2_CS: P10.1, U7.1; also elsewhere on the board
FLASH_CLK: P9.1, U5.6, U6.6, U7.6; also elsewhere on the board
FLASH_MISO: P9.2, U5.2, U6.2, U7.2; also elsewhere on the board
FLASH_MOSI: P9.3, U5.5, U6.5, U7.5; also elsewhere on the board
GND: C24.1, C25.1, C26.1, U5.4, U6.4, U7.4; also elsewhere on the board
unnamed: R13.2, U5.7
unnamed: R17.2, U6.7
unnamed: R21.2, U7.7

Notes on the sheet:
Note: Only connect one of these at once. MASTER_RESET enables simultaneous memory and processor reset, with appropriate bits set.
Triple redundant memory with configurable hold/reset. Hold will pause comms, reset will reset and can be set to be synchronous with processor reset through MASTER_RESET

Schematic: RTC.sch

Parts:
C29: 10nF; C_0402
C30: 470µF; Supercap_dual
P8: RTC_SPI; 4x01In_Header_v2
U8: AB-RTCMC-EOA9-S3; RTC_AB-RTCMC_EA09_S3
W9: CLKOUT; Test_Point
W10: RTC_OE; Test_Point
W11: RTC_INT; Test_Point

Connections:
3v3: C29.1, U8.2 (VDD); also elsewhere on the board
GIOB1: U8.7 (INT), W11.1; also elsewhere on the board
GND: C29.2, C30.2, U8.6 (GND); also elsewhere on the board
unnamed: C30.1, U8.9 (Vbackup)
unnamed: U8.1 (CLKOE), W10.1
unnamed: U8.3 (CLKOUT), W9.1
RTC_CLK: P8.2, U8.4 (SCL); also elsewhere on the board
RTC_CS: P8.1, U8.8 (CE); also elsewhere on the board
RTC_MISO: P8.3, U8.5 (SDO); also elsewhere on the board
RTC_MOSI: P8.4, U8.10 (SDI); also elsewhere on the board
